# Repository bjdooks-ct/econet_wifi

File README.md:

# Acorn Econet WiFi module

Initial work, will be more information as project moves along.

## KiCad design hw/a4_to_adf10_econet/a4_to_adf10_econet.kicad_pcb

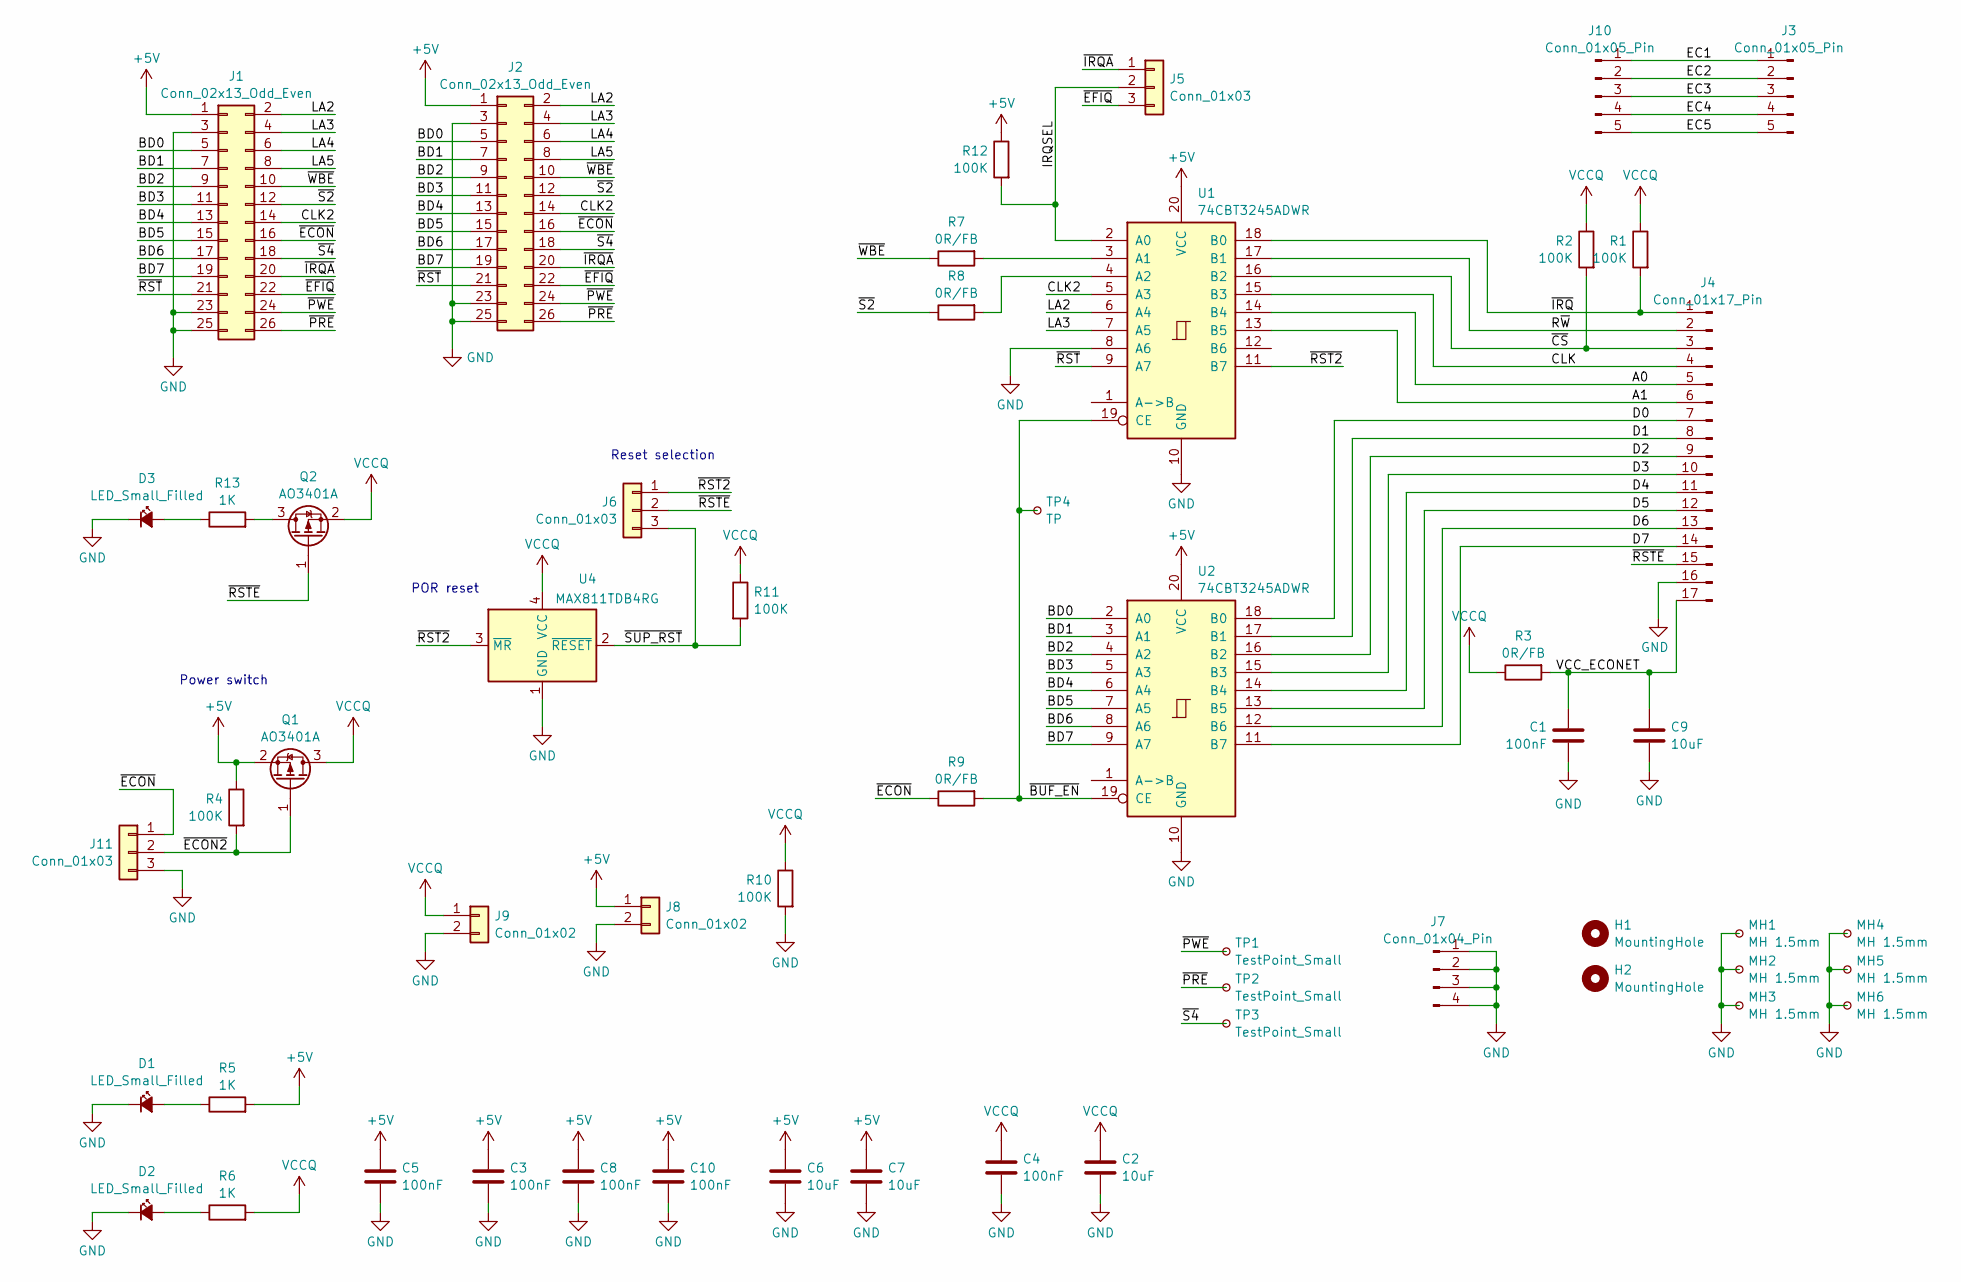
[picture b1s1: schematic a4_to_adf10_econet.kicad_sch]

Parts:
C1, C3, C4, C5, C8, C10: 100nF; C_0603_1608Metric_Pad1.08x0.95mm_HandSolder; LCSC C14663
C2, C6, C7, C9: 10uF; C_0805_2012Metric_Pad1.18x1.45mm_HandSolder; LCSC C440198
D1, D2, D3: LED_Small_Filled; LED_0603_1608Metric_Pad1.05x0.95mm_HandSolder; LCSC C2286
H1: MountingHole; MountingHole_2.5mm_Pad_TopBottom
H2: MountingHole; MountingHole_3.5mm_Pad_TopBottom
J1, J2: Conn_02x13_Odd_Even; PinHeader_2x13_P2.00mm_Vertical
J3, J10: Conn_01x05_Pin; PinSocket_1x05_P2.54mm_Vertical
J4: Conn_01x17_Pin; PinHeader_1x17_P2.54mm_Vertical
J5, J6, J11: Conn_01x03; PinHeader_1x03_P2.54mm_Vertical
J7: Conn_01x04_Pin; PinHeader_1x04_P2.54mm_Vertical
J8, J9: Conn_01x02; PinHeader_1x02_P2.54mm_Vertical
MH1, MH2, MH3, MH4, MH5, MH6: MH 1.5mm; TestPoint_Plated_Hole_D2.0mm
Q1, Q2: AO3401A; SOT-23; LCSC C15127
R1, R2, R4, R10, R11, R12: 100K; R_0603_1608Metric_Pad0.98x0.95mm_HandSolder; LCSC C25803
R3, R7, R8, R9: 0R/FB; R_0603_1608Metric_Pad0.98x0.95mm_HandSolder; LCSC C21189
R5, R6, R13: 1K; R_0603_1608Metric_Pad0.98x0.95mm_HandSolder; LCSC C21190
TP1, TP2, TP3: TestPoint_Small; TestPoint_Pad_D1.0mm
TP4: TP; TestPoint_Pad_D1.0mm
U1, U2: 74CBT3245ADWR; SOIC-20W_7.5x12.8mm_P1.27mm; LCSC C2860279
U4: MAX811TDB4RG; SOT-143; LCSC C19723717

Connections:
+5V: C3.1, C5.1, C6.1, C7.1, C8.1, C10.1, J1.1, J2.1, J8.1, Q1.2 (S), R4.1, R5.2, R12.1, U1.20 (VCC), U2.20 (VCC)
/A0: J4.5, U1.14 (B4)
/A1: J4.6, U1.13 (B5)
/BD0: J1.5, J2.5, U2.2 (A0)
/BD1: J1.7, J2.7, U2.3 (A1)
/BD2: J1.9, J2.9, U2.4 (A2)
/BD3: J1.11, J2.11, U2.5 (A3)
/BD4: J1.13, J2.13, U2.6 (A4)
/BD5: J1.15, J2.15, U2.7 (A5)
/BD6: J1.17, J2.17, U2.8 (A6)
/BD7: J1.19, J2.19, U2.9 (A7)
/CLK: J4.4, U1.15 (B3)
/CLK2: J1.14, J2.14, U1.5 (A3)
/D0: J4.7, U2.18 (B0)
/D1: J4.8, U2.17 (B1)
/D2: J4.9, U2.16 (B2)
/D3: J4.10, U2.15 (B3)
/D4: J4.11, U2.14 (B4)
/D5: J4.12, U2.13 (B5)
/D6: J4.13, U2.12 (B6)
/D7: J4.14, U2.11 (B7)
/EC1: J3.1, J10.1
/EC2: J3.2, J10.2
/EC3: J3.3, J10.3
/EC4: J3.4, J10.4
/EC5: J3.5, J10.5
/IRQSEL: J5.2, R12.2, U1.2 (A0)
/LA2: J1.2, J2.2, U1.6 (A4)
/LA3: J1.4, J2.4, U1.7 (A5)
/LA4: J1.6, J2.6
/LA5: J1.8, J2.8
/R~W: J4.2, U1.17 (B1)
/VCC_ECONET: C1.1, C9.1, J4.17, R3.2
/~BUF_EN: R9.2, TP4.1, U1.19 (CE), U2.19 (CE)
/~CS: J4.3, R2.2, U1.16 (B2)
/~ECON2: J11.2, Q1.1 (G), R4.2
/~ECON: J1.16, J2.16, J11.1, R9.1
/~EFIQ: J1.22, J2.22, J5.3
/~IRQA: J1.20, J2.20, J5.1
/~IRQ: J4.1, R1.2, U1.18 (B0)
/~PRE: J1.26, J2.26, TP2.1
/~PWE: J1.24, J2.24, TP1.1
/~RST2: J6.1, U1.11 (B7), U4.3 (~MR)
/~RSTE: J4.15, J6.2, Q2.1 (G)
/~RST: J1.21, J2.21, U1.9 (A7)
/~S2: J1.12, J2.12, R8.1
/~S4: J1.18, J2.18, TP3.1
/~SUP_RST: J6.3, R11.2, U4.2 (~RESET)
/~WBE: J1.10, J2.10, R7.1
GND: C1.2, C2.2, C3.2, C4.2, C5.2, C6.2, C7.2, C8.2, C9.2, C10.2, D1.1 (K), D2.1 (K), D3.1 (K), J1.3, J1.23, J1.25, J2.3, J2.23, J2.25, J4.16, J7.1, J7.2, J7.3, J7.4, J8.2, J9.2, J11.3, MH1.1, MH2.1, MH3.1, MH4.1, MH5.1, MH6.1, R10.2, U1.8 (A6), U1.10 (GND), U2.10 (GND), U4.1 (GND)
unnamed: D1.2 (A), R5.1
unnamed: D2.2 (A), R6.1
unnamed: D3.2 (A), R13.1
unnamed: Q2.3 (D), R13.2
unnamed: R7.2, U1.3 (A1)
unnamed: R8.2, U1.4 (A2)
VCCQ: C2.1, C4.1, J9.1, Q1.3 (D), Q2.2 (S), R1.1, R2.1, R3.1, R6.2, R10.1, R11.1, U4.4 (VCC)

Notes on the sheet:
Power switch
Reset selection
POR reset

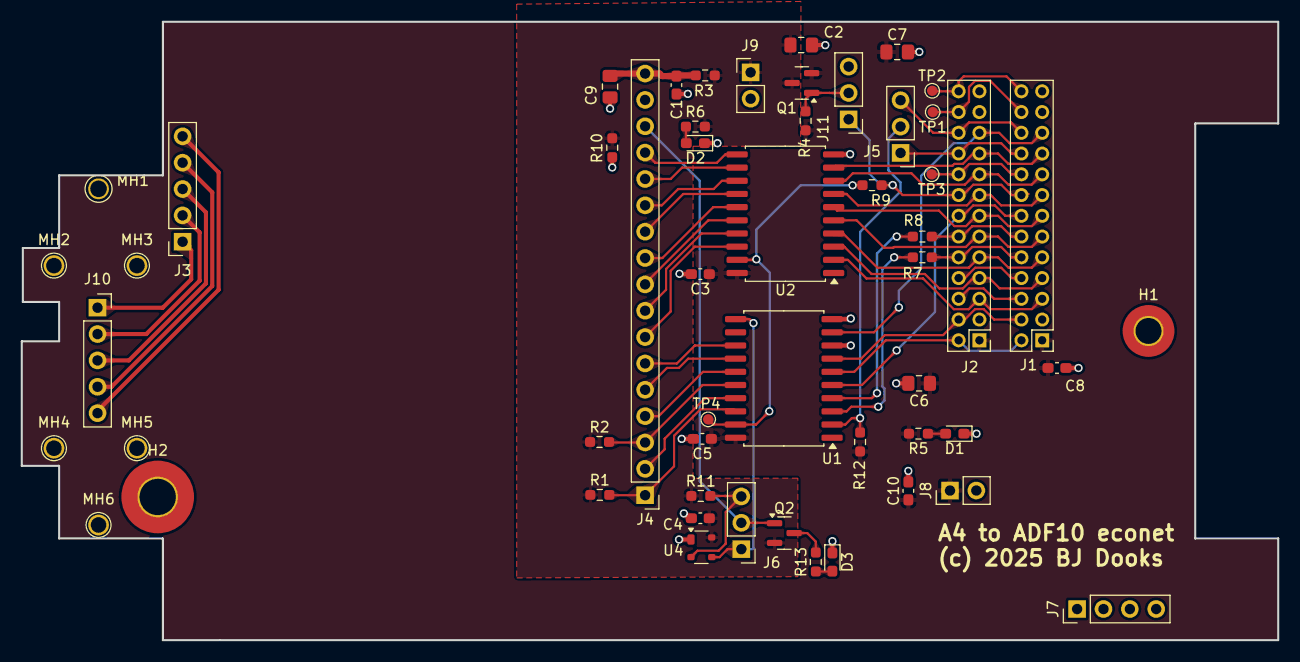
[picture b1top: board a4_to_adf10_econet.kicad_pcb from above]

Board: 2 copper layers, 121.1 x 59.6 mm, 54 parts (0 on the bottom side), 57 nets.

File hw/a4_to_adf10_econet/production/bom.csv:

Designator,Footprint,Quantity,Value,LCSC Part #
"C1, C10, C3, C4, C5, C8",0603,6,100nF,C14663
"C2, C6, C7, C9",0805,4,10uF,C440198
"D1, D2, D3",0603,3,LED_Small_Filled,C2286
"J1, J2",PinHeader_2x13_P2.00mm_Vertical,2,Conn_02x13_Odd_Even,
"J10, J3",PinSocket_1x05_P2.54mm_Vertical,2,Conn_01x05_Pin,
"J11, J5, J6",PinHeader_1x03_P2.54mm_Vertical,3,Conn_01x03,
J4,PinHeader_1x17_P2.54mm_Vertical,1,Conn_01x17_Pin,
J7,PinHeader_1x04_P2.54mm_Vertical,1,Conn_01x04_Pin,
"J8, J9",PinHeader_1x02_P2.54mm_Vertical,2,Conn_01x02,
"MH1, MH2, MH3, MH4, MH5, MH6",TestPoint_Plated_Hole_D2.0mm,6,MH 1.5mm,
"Q1, Q2",SOT-23,2,AO3401A,C15127
"R1, R10, R11, R12, R2, R4",0603,6,100K,C25803
"R13, R5, R6",0603,3,1K,C21190
"R3, R7, R8, R9",0603,4,0R/FB,C21189
"TP1, TP2, TP3",TestPoint_Pad_D1.0mm,3,TestPoint_Small,
TP4,TestPoint_Pad_D1.0mm,1,TP,
"U1, U2",SOIC-20W_7.5x12.8mm_P1.27mm,2,74CBT3245ADWR,C2860279
U4,SOT-143,1,MAX811TDB4RG,C19723717

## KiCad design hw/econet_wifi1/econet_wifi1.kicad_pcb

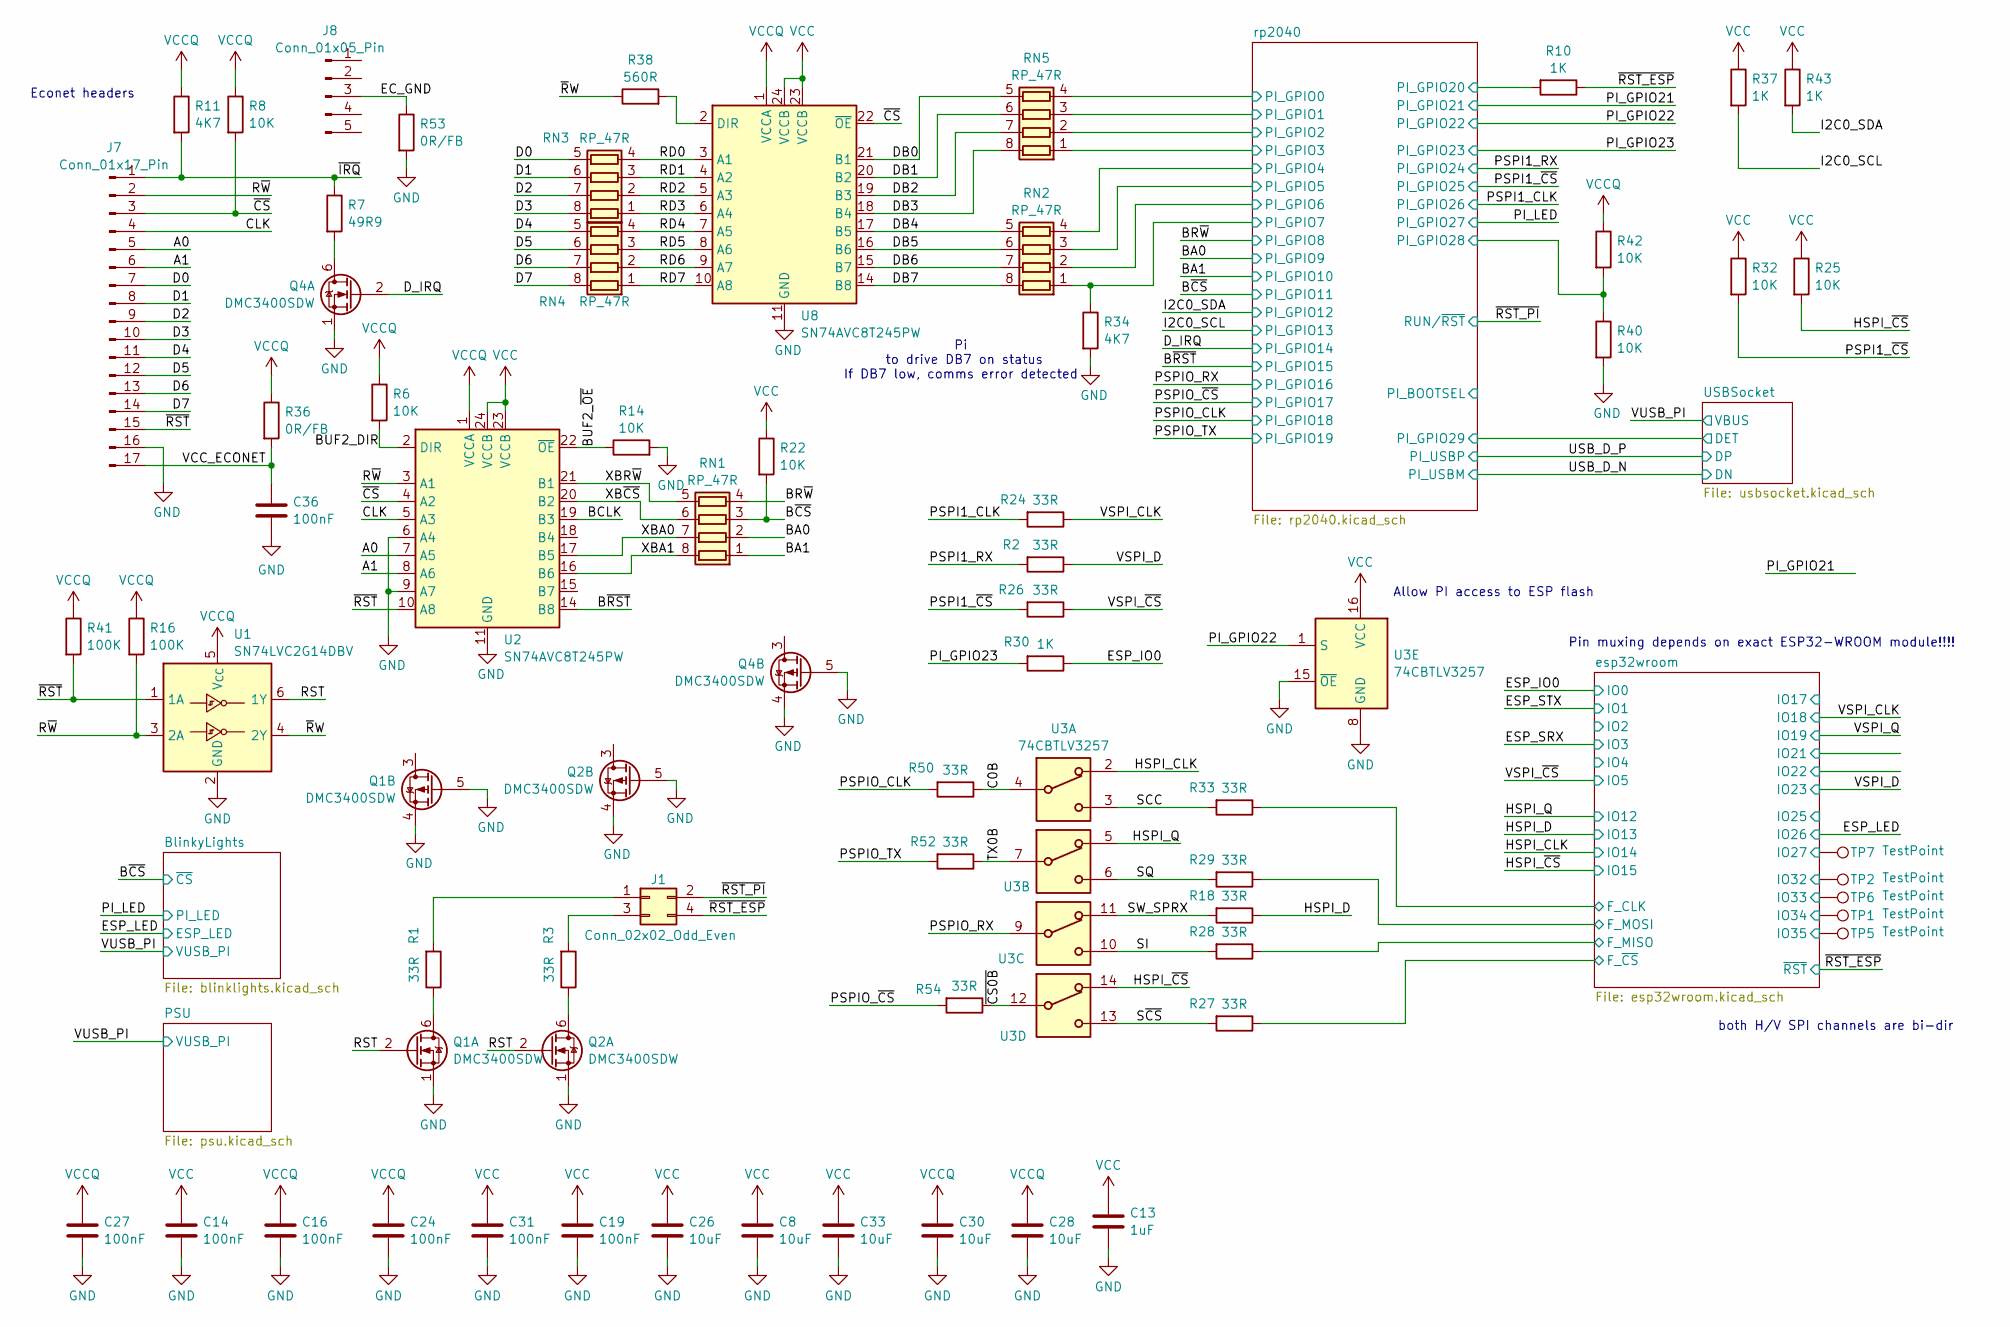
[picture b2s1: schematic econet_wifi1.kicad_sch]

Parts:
C8, C26, C28, C30, C33: 10uF; C_0805_2012Metric_Pad1.18x1.45mm_HandSolder; LCSC C440198
C13: 1uF; C_0402_1005Metric_Pad0.74x0.62mm_HandSolder; LCSC C52923
C14, C19: 100nF; C_0402_1005Metric_Pad0.74x0.62mm_HandSolder; LCSC C1525
C16, C24, C27, C31, C36: 100nF; C_0603_1608Metric_Pad1.08x0.95mm_HandSolder; LCSC C14663
J1: Conn_02x02_Odd_Even; PinHeader_2x02_P2.54mm_Vertical
J7: Conn_01x17_Pin; PinHeader_1x17_P2.54mm_Vertical
J8: Conn_01x05_Pin; PinHeader_1x05_P2.54mm_Vertical
Q1, Q2, Q4: DMC3400SDW; SOT-363_SC-70-6; LCSC C155499
R1, R2, R3, R18, R24, R26, R27, R28, R29, R33, R50, R52, R54: 33R; R_0402_1005Metric_Pad0.72x0.64mm_HandSolder; LCSC C17634
R6, R8, R14, R22, R25, R32, R40, R42: 10K; R_0603_1608Metric_Pad0.98x0.95mm_HandSolder; LCSC C25804
R7: 49R9; R_0603_1608Metric_Pad0.98x0.95mm_HandSolder; LCSC C25120
R10, R30, R37, R43: 1K; R_0603_1608Metric_Pad0.98x0.95mm_HandSolder; LCSC C21190
R11, R34: 4K7; R_0603_1608Metric_Pad0.98x0.95mm_HandSolder; LCSC C23162
R16, R41: 100K; R_0603_1608Metric_Pad0.98x0.95mm_HandSolder; LCSC C25803
R36, R53: 0R/FB; R_0603_1608Metric_Pad0.98x0.95mm_HandSolder; LCSC C21189
R38: 560R; R_0603_1608Metric_Pad0.98x0.95mm_HandSolder; LCSC C23204
RN1, RN2, RN3, RN4, RN5: RP_47R; R_Array_Concave_4x0603; LCSC C1980
TP1, TP2, TP5, TP6, TP7: TestPoint; TestPoint_Pad_D1.0mm
U1: SN74LVC2G14DBV; SOT-23-6; LCSC C12401
U2, U8: SN74AVC8T245PW; TSSOP-24_4.4x7.8mm_P0.65mm; LCSC C1523276
U3: 74CBTLV3257; TSSOP-16_4.4x5mm_P0.65mm; LCSC C7637

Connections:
/A0: J7.5, U2.7 (A5)
/A1: J7.6, U2.8 (A6)
/BA0: RN1.2 (R2.1); also elsewhere on the board
/BA1: RN1.1 (R1.1); also elsewhere on the board
/BCLK: U2.19 (B3)
/BR~W: RN1.4 (R4.1); also elsewhere on the board
/BUF2_DIR: R6.2, U2.2 (DIR)
/BUF2_~OE: R14.1, U2.22 (~OE)
/B~CS: R22.2, RN1.3 (R3.1); also elsewhere on the board
/B~RST: U2.14 (B8); also elsewhere on the board
/C0B: R50.1, U3.4
/CLK: J7.4, U2.5 (A3)
/D0: J7.7, RN3.5 (R4.2)
/D1: J7.8, RN3.6 (R3.2)
/D2: J7.9, RN3.7 (R2.2)
/D3: J7.10, RN3.8 (R1.2)
/D4: J7.11, RN4.5 (R4.2)
/D5: J7.12, RN4.6 (R3.2)
/D6: J7.13, RN4.7 (R2.2)
/D7: J7.14, RN4.8 (R1.2)
/DB0: RN5.5 (R4.2), U8.21 (B1)
/DB1: RN5.6 (R3.2), U8.20 (B2)
/DB2: RN5.7 (R2.2), U8.19 (B3)
/DB3: RN5.8 (R1.2), U8.18 (B4)
/DB4: RN2.5 (R4.2), U8.17 (B5)
/DB5: RN2.6 (R3.2), U8.16 (B6)
/DB6: RN2.7 (R2.2), U8.15 (B7)
/DB7: RN2.8 (R1.2), U8.14 (B8)
/D_IRQ: Q4.2 (G); also elsewhere on the board
/EC_GND: J8.3, R53.1
/ESP_IO0: R30.1; also elsewhere on the board
/HSPI_CLK: U3.2; also elsewhere on the board
/HSPI_D: R18.1; also elsewhere on the board
/HSPI_Q: U3.5; also elsewhere on the board
/HSPI_~CS: R25.2, U3.14; also elsewhere on the board
/I2C0_SCL: R37.2; also elsewhere on the board
/I2C0_SDA: R43.2; also elsewhere on the board
/PI_GPIO22: U3.1 (S); also elsewhere on the board
/PI_GPIO23: R30.2; also elsewhere on the board
/PSPI1_CLK: R24.2; also elsewhere on the board
/PSPI1_RX: R2.2; also elsewhere on the board
/PSPI1_~CS: R26.2, R32.2; also elsewhere on the board
/PSPIO_CLK: R50.2; also elsewhere on the board
/PSPIO_RX: U3.9; also elsewhere on the board
/PSPIO_TX: R52.2; also elsewhere on the board
/PSPIO_~CS: R54.2; also elsewhere on the board
/RD0: RN3.4 (R4.1), U8.3 (A1)
/RD1: RN3.3 (R3.1), U8.4 (A2)
/RD2: RN3.2 (R2.1), U8.5 (A3)
/RD3: RN3.1 (R1.1), U8.6 (A4)
/RD4: RN4.4 (R4.1), U8.7 (A5)
/RD5: RN4.3 (R3.1), U8.8 (A6)
/RD6: RN4.2 (R2.1), U8.9 (A7)
/RD7: RN4.1 (R1.1), U8.10 (A8)
/RST: Q1.2 (G), Q2.2 (G), U1.6 (1Y)
/R~W: J7.2, R16.2, U1.3 (2A), U2.3 (A1)
/SCC: R33.2, U3.3
/SI: R28.2, U3.10
/SQ: R29.2, U3.6
/SW_SPRX: R18.2, U3.11
/S~CS: R27.2, U3.13
/TX0B: R52.1, U3.7
/VCC_ECONET: C36.1, J7.17, R36.2
/VSPI_CLK: R24.1; also elsewhere on the board
/VSPI_D: R2.1; also elsewhere on the board
/VSPI_~CS: R26.1; also elsewhere on the board
/XBA0: RN1.7 (R2.2), U2.17 (B5)
/XBA1: RN1.8 (R1.2), U2.16 (B6)
/XBR~W: RN1.5 (R4.2), U2.21 (B1)
/XB~CS: RN1.6 (R3.2), U2.20 (B2)
/esp32wroom/F_CLK: R33.1; also elsewhere on the board
/esp32wroom/F_MISO: R28.1; also elsewhere on the board
/esp32wroom/F_MOSI: R29.1; also elsewhere on the board
/esp32wroom/F_~CS: R27.1; also elsewhere on the board
/esp32wroom/IO27: TP7.1; also elsewhere on the board
/esp32wroom/IO32: TP2.1; also elsewhere on the board
/esp32wroom/IO33: TP6.1; also elsewhere on the board
/esp32wroom/IO34: TP1.1; also elsewhere on the board
/esp32wroom/IO35: TP5.1; also elsewhere on the board
/rp2040/PI_GPIO0: RN5.4 (R4.1); also elsewhere on the board
/rp2040/PI_GPIO1: RN5.3 (R3.1); also elsewhere on the board
/rp2040/PI_GPIO2: RN5.2 (R2.1); also elsewhere on the board
/rp2040/PI_GPIO3: RN5.1 (R1.1); also elsewhere on the board
/rp2040/PI_GPIO4: RN2.4 (R4.1); also elsewhere on the board
/rp2040/PI_GPIO5: RN2.3 (R3.1); also elsewhere on the board
/rp2040/PI_GPIO6: RN2.2 (R2.1); also elsewhere on the board
/rp2040/PI_GPIO7: R34.1, RN2.1 (R1.1); also elsewhere on the board
/rp2040/PI_GPIO20: R10.2; also elsewhere on the board
/rp2040/PI_GPIO28: R40.1, R42.2; also elsewhere on the board
/~CS0B: R54.1, U3.12
/~CS: J7.3, R8.2, U2.4 (A2), U8.22 (~OE)
/~IRQ: J7.1, R7.1, R11.2
/~RST_ESP: J1.4, R10.1; also elsewhere on the board
/~RST_PI: J1.2; also elsewhere on the board
/~RST: J7.15, R41.2, U1.1 (1A), U2.10 (A8)
/~RW: R38.1, U1.4 (2Y)
GND: C8.2, C13.2, C14.2, C16.2, C19.2, C24.2, C26.2, C27.2, C28.2, C30.2, C31.2, C33.2, C36.2, J7.16, Q1.1, Q1.4 (S), Q1.5 (G), Q2.1, Q2.4 (S), Q2.5 (G), Q4.1, Q4.4 (S), Q4.5 (G), R14.2, R34.2, R40.2, R53.2, U1.2 (GND), U2.6 (A4), U2.9 (A7), U2.11 (GND), U2.12 (GND), U2.13 (GND), U3.8 (GND), U3.15 (~OE), U8.11 (GND), U8.12 (GND), U8.13 (GND); also elsewhere on the board
unnamed: J1.1, R1.2
unnamed: J1.3, R3.2
unnamed: Q1.6 (D), R1.1
unnamed: Q2.6 (D), R3.1
unnamed: Q4.6 (D), R7.2
unnamed: R38.2, U8.2 (DIR)
VCC: C8.1, C13.1, C14.1, C19.1, C26.1, C31.1, C33.1, R22.1, R25.1, R32.1, R37.1, R43.1, U2.23 (VCCB), U2.24 (VCCB), U3.16 (VCC), U8.23 (VCCB), U8.24 (VCCB); also elsewhere on the board
VCCQ: C16.1, C24.1, C27.1, C28.1, C30.1, R6.1, R8.1, R11.1, R16.1, R36.1, R41.1, R42.1, U1.5 (V_{CC}), U2.1 (VCCA), U8.1 (VCCA); also elsewhere on the board

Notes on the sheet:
Econet headers
Pi to drive DB7 on status If DB7 low, comms error detected
Pin muxing depends on exact ESP32-WROOM module!!!!
Allow PI access to ESP flash
both H/V SPI channels are bi-dir

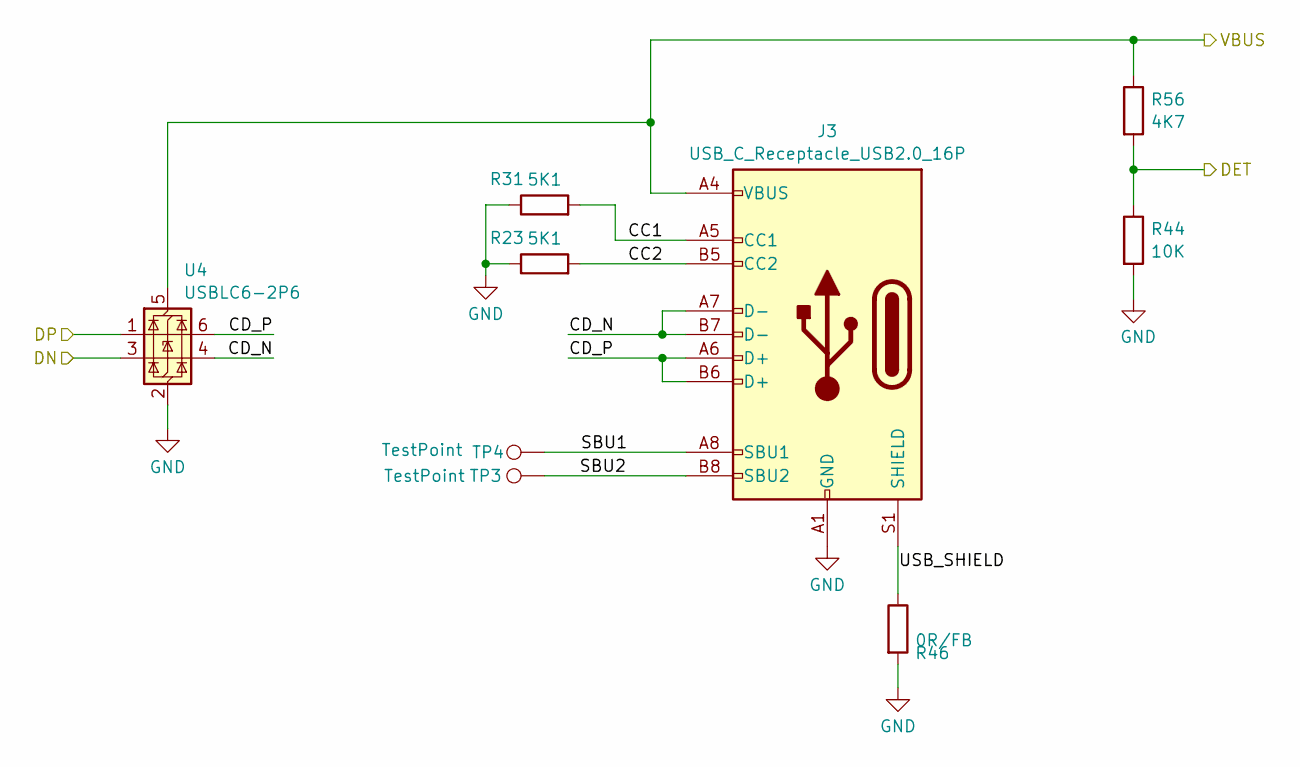
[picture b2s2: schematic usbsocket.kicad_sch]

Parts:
J3: USB_C_Receptacle_USB2.0_16P; USB_C_Receptacle_HCTL_HC-TYPE-C-16P-01A; LCSC C2894897
R23, R31: 5K1; R_0402_1005Metric_Pad0.72x0.64mm_HandSolder; LCSC C25905
R44: 10K; R_0603_1608Metric_Pad0.98x0.95mm_HandSolder; LCSC C25804
R46: 0R/FB; R_0603_1608Metric_Pad0.98x0.95mm_HandSolder; LCSC C21189
R56: 4K7; R_0603_1608Metric_Pad0.98x0.95mm_HandSolder; LCSC C23162
TP3, TP4: TestPoint; TestPoint_Pad_D1.0mm
U4: USBLC6-2P6; SOT-666; LCSC C5180249

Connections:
/USBSocket/CC1: J3.A5 (CC1), R31.2
/USBSocket/CC2: J3.B5 (CC2), R23.2
/USBSocket/CD_N: J3.A7 (D-), J3.B7 (D-), U4.4 (I/O2)
/USBSocket/CD_P: J3.A6 (D+), J3.B6 (D+), U4.6 (I/O1)
/USBSocket/DET: R44.1, R56.2; also elsewhere on the board
/USBSocket/SBU1: J3.A8 (SBU1), TP4.1
/USBSocket/SBU2: J3.B8 (SBU2), TP3.1
/USBSocket/USB_SHIELD: J3.S1 (SHIELD), R46.1
/USB_D_N: U4.3 (I/O2); also elsewhere on the board
/USB_D_P: U4.1 (I/O1); also elsewhere on the board
/VUSB_PI: J3.A4 (VBUS), J3.A9 (VBUS), J3.B4 (VBUS), J3.B9 (VBUS), R56.1, U4.5 (VBUS); also elsewhere on the board
GND: J3.A1 (GND), J3.A12 (GND), J3.B1 (GND), J3.B12 (GND), R23.1, R31.1, R44.2, R46.2, U4.2 (GND); also elsewhere on the board

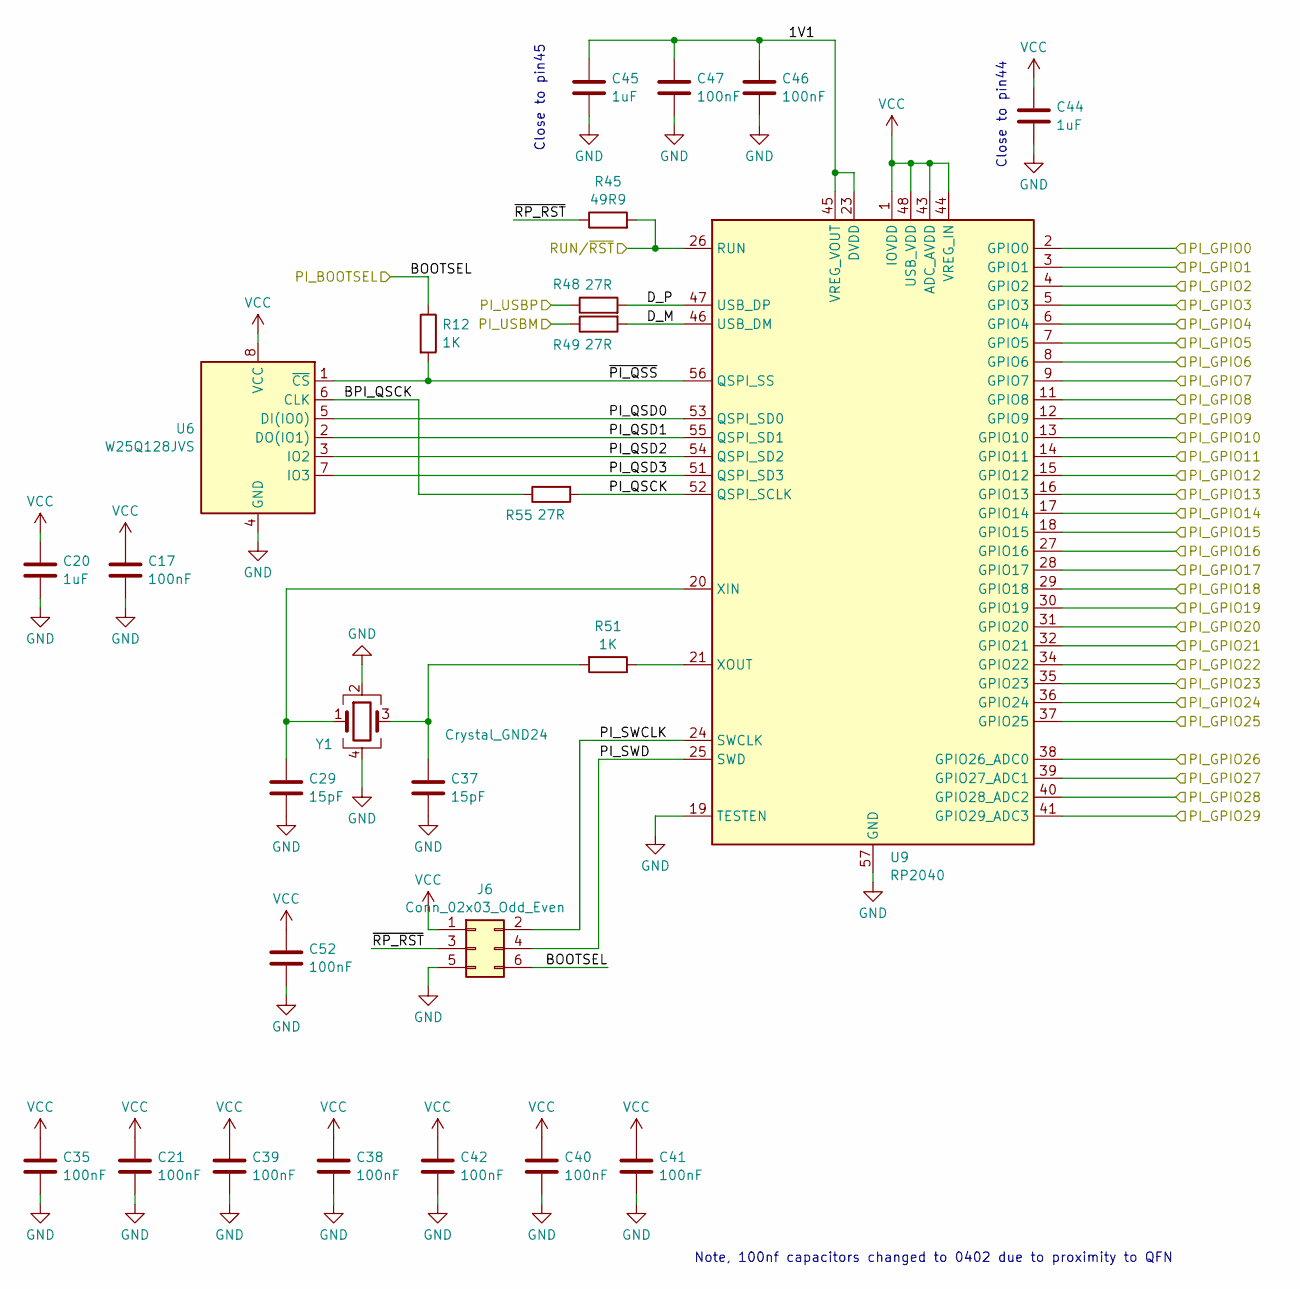
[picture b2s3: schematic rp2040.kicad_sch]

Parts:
C17, C21, C35, C38, C39, C40, C41, C42, C46, C47: 100nF; C_0402_1005Metric_Pad0.74x0.62mm_HandSolder; LCSC C1525
C20, C44, C45: 1uF; C_0402_1005Metric_Pad0.74x0.62mm_HandSolder; LCSC C52923
C29, C37: 15pF; C_0603_1608Metric_Pad1.08x0.95mm_HandSolder; LCSC C1644
C52: 100nF; C_0603_1608Metric_Pad1.08x0.95mm_HandSolder; LCSC C14663
J6: Conn_02x03_Odd_Even; PinHeader_2x03_P2.54mm_Vertical
R12, R51: 1K; R_0603_1608Metric_Pad0.98x0.95mm_HandSolder; LCSC C21190
R45: 49R9; R_0603_1608Metric_Pad0.98x0.95mm_HandSolder; LCSC C25120
R48, R49, R55: 27R; R_0402_1005Metric_Pad0.72x0.64mm_HandSolder; LCSC C25100
U6: W25Q128JVS; SOIC-8_5.23x5.23mm_P1.27mm
U9: RP2040; QFN-56-1EP_7x7mm_P0.4mm_EP3.2x3.2mm
Y1: Crystal_GND24; Crystal_SMD_Abracon_ABM8G-4Pin_3.2x2.5mm; LCSC C20625731

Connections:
/BA0: U9.12 (GPIO9); also elsewhere on the board
/BA1: U9.13 (GPIO10); also elsewhere on the board
/BR~W: U9.11 (GPIO8); also elsewhere on the board
/B~CS: U9.14 (GPIO11); also elsewhere on the board
/B~RST: U9.18 (GPIO15); also elsewhere on the board
/D_IRQ: U9.17 (GPIO14); also elsewhere on the board
/I2C0_SCL: U9.16 (GPIO13); also elsewhere on the board
/I2C0_SDA: U9.15 (GPIO12); also elsewhere on the board
/PI_GPIO21: U9.32 (GPIO21)
/PI_GPIO22: U9.34 (GPIO22); also elsewhere on the board
/PI_GPIO23: U9.35 (GPIO23); also elsewhere on the board
/PI_LED: U9.39 (GPIO27_ADC1); also elsewhere on the board
/PSPI1_CLK: U9.38 (GPIO26_ADC0); also elsewhere on the board
/PSPI1_RX: U9.36 (GPIO24); also elsewhere on the board
/PSPI1_~CS: U9.37 (GPIO25); also elsewhere on the board
/PSPIO_CLK: U9.29 (GPIO18); also elsewhere on the board
/PSPIO_RX: U9.27 (GPIO16); also elsewhere on the board
/PSPIO_TX: U9.30 (GPIO19); also elsewhere on the board
/PSPIO_~CS: U9.28 (GPIO17); also elsewhere on the board
/USBSocket/DET: U9.41 (GPIO29_ADC3); also elsewhere on the board
/USB_D_N: R49.1; also elsewhere on the board
/USB_D_P: R48.1; also elsewhere on the board
/rp2040/1V1: C45.1, C46.1, C47.1, U9.23 (DVDD), U9.45 (VREG_VOUT), U9.50 (DVDD)
/rp2040/BOOTSEL: J6.6, R12.1
/rp2040/BPI_QSCK: R55.1, U6.6 (CLK)
/rp2040/D_M: R49.2, U9.46 (USB_DM)
/rp2040/D_P: R48.2, U9.47 (USB_DP)
/rp2040/PI_GPIO0: U9.2 (GPIO0); also elsewhere on the board
/rp2040/PI_GPIO1: U9.3 (GPIO1); also elsewhere on the board
/rp2040/PI_GPIO2: U9.4 (GPIO2); also elsewhere on the board
/rp2040/PI_GPIO3: U9.5 (GPIO3); also elsewhere on the board
/rp2040/PI_GPIO4: U9.6 (GPIO4); also elsewhere on the board
/rp2040/PI_GPIO5: U9.7 (GPIO5); also elsewhere on the board
/rp2040/PI_GPIO6: U9.8 (GPIO6); also elsewhere on the board
/rp2040/PI_GPIO7: U9.9 (GPIO7); also elsewhere on the board
/rp2040/PI_GPIO20: U9.31 (GPIO20); also elsewhere on the board
/rp2040/PI_GPIO28: U9.40 (GPIO28_ADC2); also elsewhere on the board
/rp2040/PI_QSCK: R55.2, U9.52 (QSPI_SCLK)
/rp2040/PI_QSD0: U6.5 (DI(IO0)), U9.53 (QSPI_SD0)
/rp2040/PI_QSD1: U6.2 (DO(IO1)), U9.55 (QSPI_SD1)
/rp2040/PI_QSD2: U6.3 (IO2), U9.54 (QSPI_SD2)
/rp2040/PI_QSD3: U6.7 (IO3), U9.51 (QSPI_SD3)
/rp2040/PI_SWCLK: J6.2, U9.24 (SWCLK)
/rp2040/PI_SWD: J6.4, U9.25 (SWD)
/rp2040/~PI_QSS: R12.2, U6.1 (~CS), U9.56 (QSPI_SS)
/rp2040/~RP_RST: J6.3, R45.1
/~RST_PI: R45.2, U9.26 (RUN); also elsewhere on the board
GND: C17.2, C20.2, C21.2, C29.2, C35.2, C37.2, C38.2, C39.2, C40.2, C41.2, C42.2, C44.2, C45.2, C46.2, C47.2, C52.2, J6.5, U6.4 (GND), U9.19 (TESTEN), U9.57 (GND), Y1.2, Y1.4; also elsewhere on the board
unnamed: C37.1, R51.2, Y1.3
unnamed: C29.1, U9.20 (XIN), Y1.1
unnamed: R51.1, U9.21 (XOUT)
VCC: C17.1, C20.1, C21.1, C35.1, C38.1, C39.1, C40.1, C41.1, C42.1, C44.1, C52.1, J6.1, U6.8 (VCC), U9.1 (IOVDD), U9.10 (IOVDD), U9.22 (IOVDD), U9.33 (IOVDD), U9.42 (IOVDD), U9.43 (ADC_AVDD), U9.44 (VREG_IN), U9.48 (USB_VDD), U9.49 (IOVDD); also elsewhere on the board

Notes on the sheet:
Note, 100nf capacitors changed to 0402 due to proximity to QFN
Close to pin45
Close to pin44

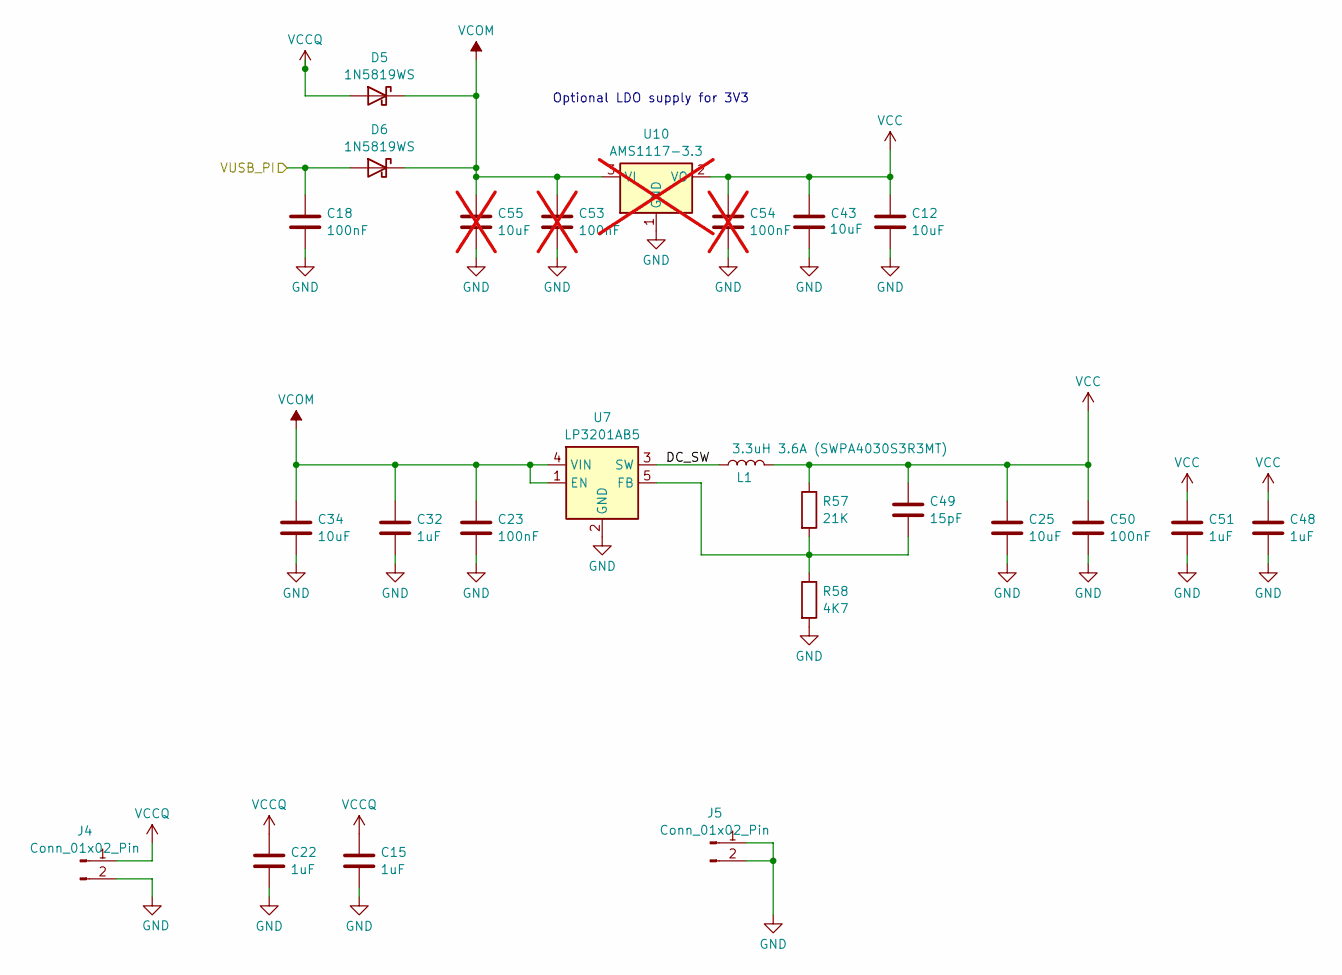
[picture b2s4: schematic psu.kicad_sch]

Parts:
C12, C25, C34, C43: 10uF; C_0805_2012Metric_Pad1.18x1.45mm_HandSolder; LCSC C440198
C15, C22, C32, C48, C51: 1uF; C_0402_1005Metric_Pad0.74x0.62mm_HandSolder; LCSC C52923
C18, C23, C50: 100nF; C_0603_1608Metric_Pad1.08x0.95mm_HandSolder; LCSC C14663
C49: 15pF; C_0603_1608Metric_Pad1.08x0.95mm_HandSolder; LCSC C1644
C53, C54: 100nF; C_0603_1608Metric_Pad1.08x0.95mm_HandSolder; LCSC C14663; not fitted
C55: 10uF; C_0805_2012Metric_Pad1.18x1.45mm_HandSolder; LCSC C440198; not fitted
D5, D6: 1N5819WS; D_SOD-323; LCSC C191023
J4, J5: Conn_01x02_Pin; PinHeader_1x02_P2.54mm_Vertical
L1: 3.3uH 3.6A (SWPA4030S3R3MT); L_APV_ANR5040; LCSC C15269
R57: 21K; R_0603_1608Metric_Pad0.98x0.95mm_HandSolder; LCSC C22956
R58: 4K7; R_0603_1608Metric_Pad0.98x0.95mm_HandSolder; LCSC C23162
U7: LP3201AB5; SOT-23-5; LCSC C2890377
U10: AMS1117-3.3; SOT-223-3_TabPin2; not fitted

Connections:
/PSU/DC_SW: L1.1, U7.3 (SW)
/VUSB_PI: C18.1, D6.2 (A); also elsewhere on the board
GND: C12.2, C15.2, C18.2, C22.2, C23.2, C25.2, C32.2, C34.2, C43.2, C48.2, C50.2, C51.2, C53.2, C54.2, C55.2, J4.2, J5.1, J5.2, R58.2, U7.2 (GND), U10.1 (GND); also elsewhere on the board
unnamed: C49.2, R57.2, R58.1, U7.5 (FB)
VCC: C12.1, C25.1, C43.1, C48.1, C49.1, C50.1, C51.1, C54.1, L1.2, R57.1, U10.2 (VO); also elsewhere on the board
VCCQ: C15.1, C22.1, D5.2 (A), J4.1; also elsewhere on the board
VCOM: C23.1, C32.1, C34.1, C53.1, C55.1, D5.1 (K), D6.1 (K), U7.1 (EN), U7.4 (VIN), U10.3 (VI)

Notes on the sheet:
Optional LDO supply for 3V3

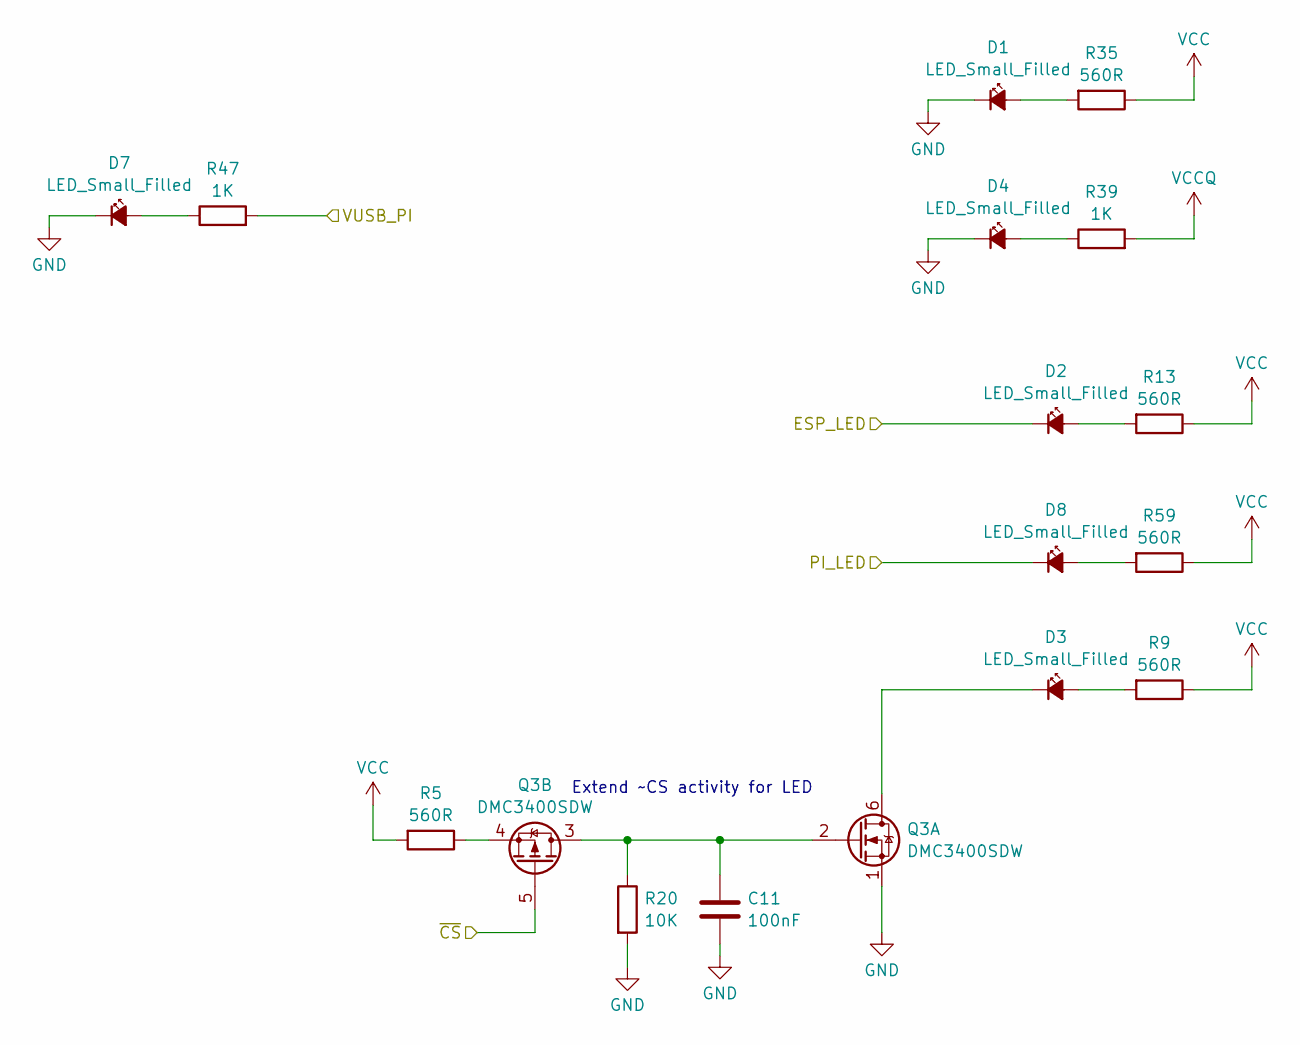
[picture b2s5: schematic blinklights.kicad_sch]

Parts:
C11: 100nF; C_0603_1608Metric_Pad1.08x0.95mm_HandSolder; LCSC C14663
D1, D2, D3, D4, D7, D8: LED_Small_Filled; LED_0603_1608Metric_Pad1.05x0.95mm_HandSolder; LCSC C2286
Q3: DMC3400SDW; SOT-363_SC-70-6; LCSC C155499
R5, R9, R13, R35, R59: 560R; R_0603_1608Metric_Pad0.98x0.95mm_HandSolder; LCSC C23204
R20: 10K; R_0603_1608Metric_Pad0.98x0.95mm_HandSolder; LCSC C25804
R39, R47: 1K; R_0603_1608Metric_Pad0.98x0.95mm_HandSolder; LCSC C21190

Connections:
/B~CS: Q3.5 (G); also elsewhere on the board
/ESP_LED: D2.1 (K); also elsewhere on the board
/PI_LED: D8.1 (K); also elsewhere on the board
/VUSB_PI: R47.2; also elsewhere on the board
GND: C11.2, D1.1 (K), D4.1 (K), D7.1 (K), Q3.1, R20.2; also elsewhere on the board
unnamed: D1.2 (A), R35.2
unnamed: D2.2 (A), R13.2
unnamed: D3.2 (A), R9.2
unnamed: D3.1 (K), Q3.6 (D)
unnamed: D4.2 (A), R39.1
unnamed: D7.2 (A), R47.1
unnamed: D8.2 (A), R59.2
unnamed: C11.1, Q3.2 (G), Q3.3 (D), R20.1
unnamed: Q3.4 (S), R5.1
VCC: R5.2, R9.1, R13.1, R35.1, R59.1; also elsewhere on the board
VCCQ: R39.2; also elsewhere on the board

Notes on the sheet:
Extend ~CS activity for LED

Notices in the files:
hw/a4_to_adf10_econet/a4_to_adf10_econet.kicad_pcb:
(c) 2025 BJ Dooks
hw/econet_wifi1/econet_wifi1.kicad_pcb:
(c) 2025 Ben Dooks
